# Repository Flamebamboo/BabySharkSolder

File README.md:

# BabySharkSolder

This project is a keychain baby shark! I've designed it specifically for my baby sister because she absolutely adores the Baby Shark cartoon. Can't wait to attach it to her backpack!

BOM 
- 4x LED's
- 4x Resistors
- 1x Battery cell
- 1x Motor DC
- 1x SW_PUSH

By FlameBamboo

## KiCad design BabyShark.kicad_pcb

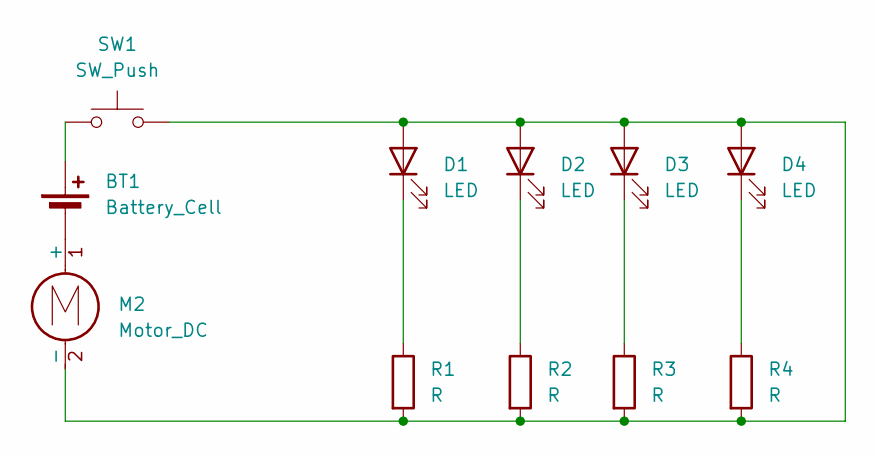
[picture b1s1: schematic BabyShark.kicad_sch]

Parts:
BT1: Battery_Cell; BatteryHolder_Keystone_3034_1x20mm
D1, D2, D3, D4: LED; LED_D5.0mm
M2: Motor_DC; PinHeader_1x02_P2.54mm_Vertical
R1, R2, R3, R4: R; R_Axial_DIN0207_L6.3mm_D2.5mm_P7.62mm_Horizontal
SW1: SW_Push; SW_PUSH_6mm

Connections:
unnamed: BT1.1 (+), SW1.1
unnamed: BT1.2 (-), M2.1 (+)
unnamed: D1.2 (A), D2.2 (A), D3.2 (A), D4.2 (A), M2.2 (-), R1.2, R2.2, R3.2, R4.2, SW1.2
unnamed: D1.1 (K), R1.1
unnamed: D2.1 (K), R2.1
unnamed: D3.1 (K), R3.1
unnamed: D4.1 (K), R4.1

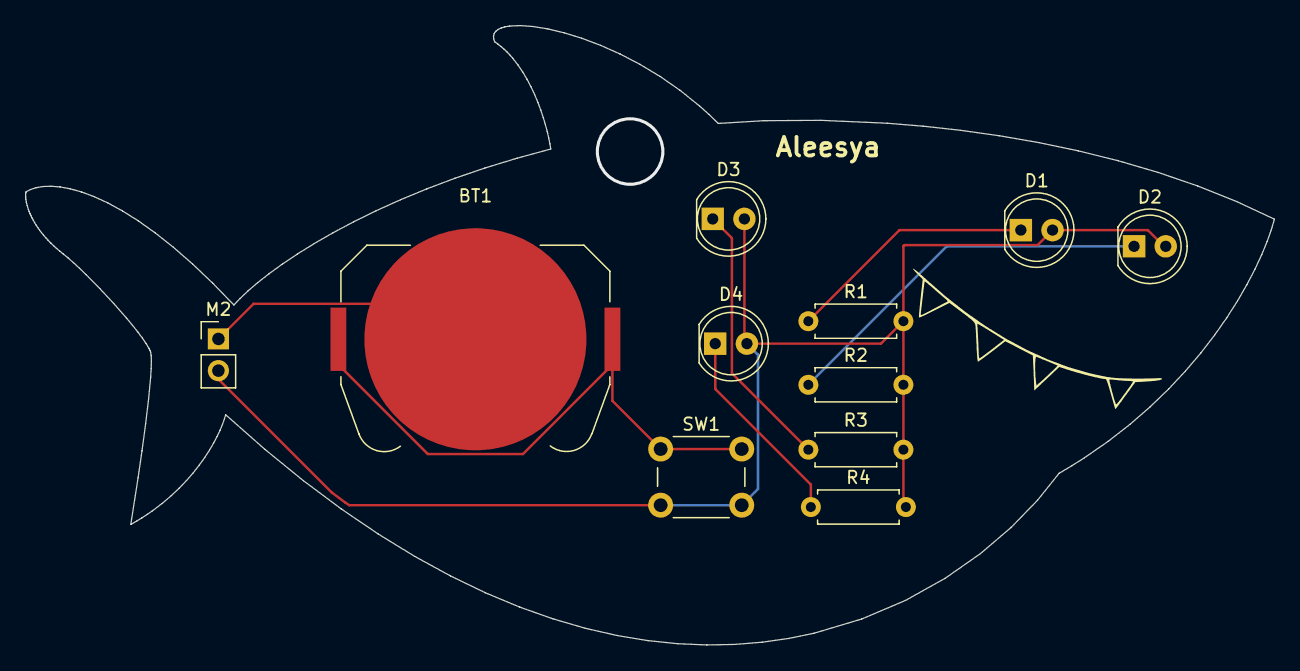
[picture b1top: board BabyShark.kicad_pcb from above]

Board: 2 copper layers, 100.1 x 49.7 mm, 11 parts (0 on the bottom side), 7 nets.

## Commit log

2025-06-22 added desc & BOM
2025-06-22 Project screenshots
2025-06-22 gerbes zip added
2025-06-24 Updated PCB
2025-08-24 addes sources
